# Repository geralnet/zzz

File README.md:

zZz
===

Geral.NET zZz Home Automation

PLEASE NOTE:
You are free to help us and we are glad you do;
however, you abdcate any intellectual property or ownership of
any material you submit to us. We will gladly take it as a without-strings attached donation.

*** This project is at version 0.0, so yeah, just started! ***

- HARDWARE
All schematics and DYO (easy to homebrew) board layouts are provided.
Not required, but suggested connection to an Arduino (ethernet model or with shield).

- FIRMWARE
Basic controller for Arduino with Ethernet provided with source code.
Your can adapt it further according to your needs.

- COMPUTER SOFTWARE
Java cross-platform control software.
The source code is provided and you are free to adapt to your needs.

- TABLET / SMARTPHONE APPS
The source code of all apps will be distributed.
Please note that our official app may not be free to download,
but you can compile and install it on your own (instructions provided).

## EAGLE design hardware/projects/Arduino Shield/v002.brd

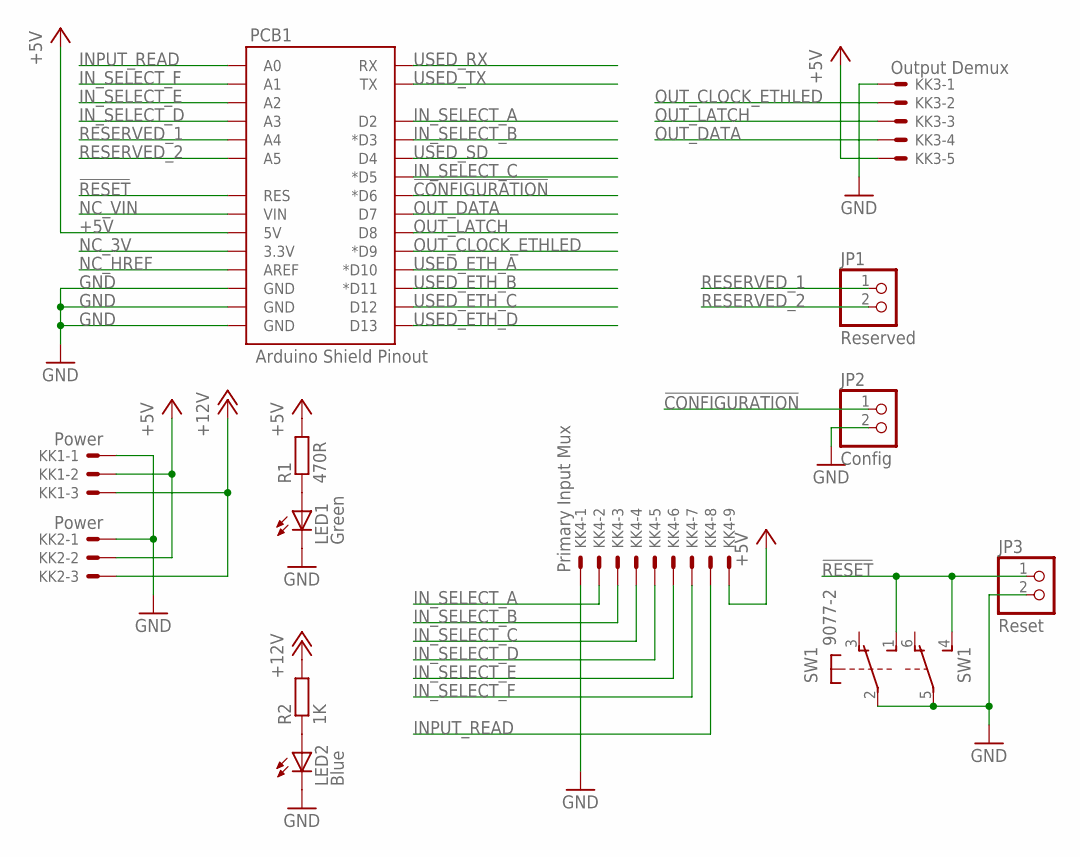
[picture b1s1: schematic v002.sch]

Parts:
JP1: Reserved; 1X02
JP2: Config; 1X02
JP3: Reset; 1X02
KK1, KK2: Power; 6410-03
KK3: Output Demux; 6410-05
KK4: Primary Input Mux; 6410-09
LED1: Green; LED3MM
LED2: Blue; LED3MM
PCB1: Arduino Shield Pinout; DUEMILANOVE_SHIELD_LONGPADS
R1: 470R; 0204/7
R2: 1K; 0204/7
SW1: 9077-2

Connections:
!CONFIGURATION: JP2.1, PCB1.D6 (*D6)
!RESET: JP3.1, PCB1.RES, SW1.1 (S), SW1.4 (S)
+5V: KK1.2, KK2.2, KK3.5, KK4.9, PCB1.5V, R1.2
+12V: KK1.3, KK2.3, R2.2
GND: JP2.2, JP3.2, KK1.1, KK2.1, KK3.1, KK4.1, LED1.K (C), LED2.K (C), PCB1.GND@0 (GND), PCB1.GND@1 (GND), PCB1.GND@2 (GND), SW1.2, SW1.5
INPUT_READ: KK4.8, PCB1.A0
IN_SELECT_A: KK4.2, PCB1.D2
IN_SELECT_B: KK4.3, PCB1.D3 (*D3)
IN_SELECT_C: KK4.4, PCB1.D5 (*D5)
IN_SELECT_D: KK4.5, PCB1.A3
IN_SELECT_E: KK4.6, PCB1.A2
IN_SELECT_F: KK4.7, PCB1.A1
N-L1: LED1.A, R1.1
N-L2: LED2.A, R2.1
NC_3V: PCB1.3.3V
NC_HREF: PCB1.AREF
NC_VIN: PCB1.VIN
OUT_CLOCK_ETHLED: KK3.2, PCB1.D9 (*D9)
OUT_DATA: KK3.4, PCB1.D7
OUT_LATCH: KK3.3, PCB1.D8
RESERVED_1: JP1.1, PCB1.A4
RESERVED_2: JP1.2, PCB1.A5
USED_ETH_A: PCB1.D10 (*D10)
USED_ETH_B: PCB1.D11 (*D11)
USED_ETH_C: PCB1.D12
USED_ETH_D: PCB1.D13
USED_RX: PCB1.RX
USED_SD: PCB1.D4
USED_TX: PCB1.TX

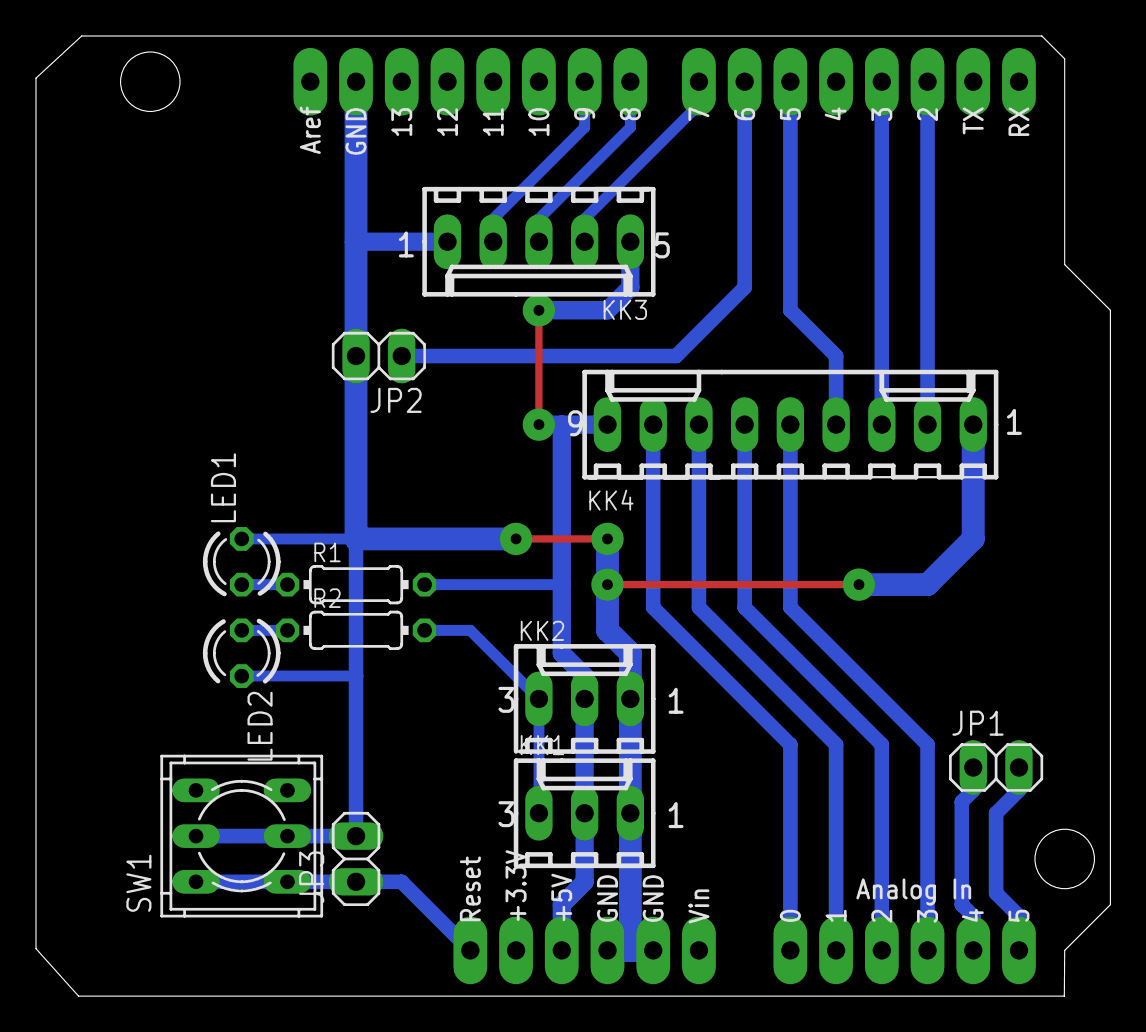
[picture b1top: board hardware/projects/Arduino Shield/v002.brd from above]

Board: 2 copper layers, 59.7 x 53.3 mm, 13 parts (0 on the bottom side), 19 nets.

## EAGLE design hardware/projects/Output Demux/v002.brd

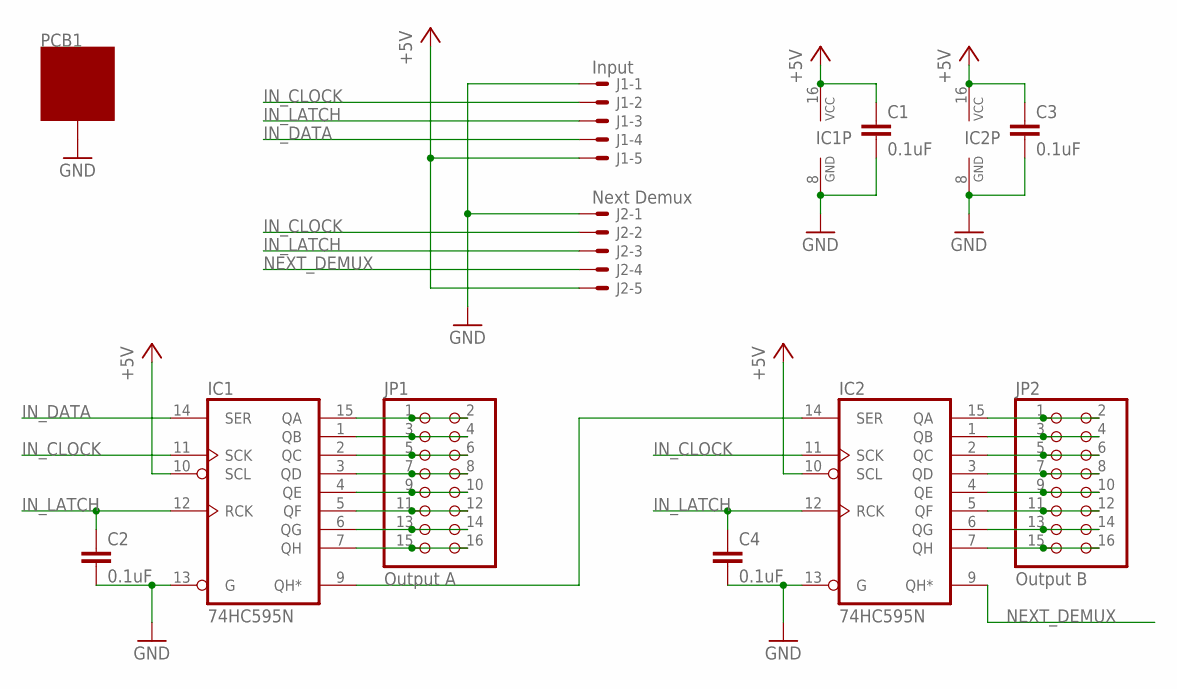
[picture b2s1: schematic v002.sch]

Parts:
C1, C2, C3, C4: 0.1uF; C050-024X044
IC1, IC2: 74HC595N; DIL16
J1: Input; 6410-05
J2: Next Demux; 6410-05
JP1: Output A; 2X08
JP2: Output B; 2X08
PCB1: ZZZ_MODULE05X05; ZZZ_MODULE_05X05

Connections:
+5V: C1.1, C3.1, IC1.10 (SCL), IC1.16 (VCC), IC2.10 (SCL), IC2.16 (VCC), J1.5, J2.5
GND: C1.2, C2.2, C3.2, C4.2, IC1.8 (GND), IC1.13 (G), IC2.8 (GND), IC2.13 (G), J1.1, J2.1, PCB1.GND@1, PCB1.GND@2, PCB1.GND@3, PCB1.GND@4, PCB1.GND@5, PCB1.GND@6, PCB1.GND@7, PCB1.GND@8
IN_CLOCK: IC1.11 (SCK), IC2.11 (SCK), J1.2, J2.2
IN_DATA: IC1.14 (SER), J1.4
IN_LATCH: C2.1, C4.1, IC1.12 (RCK), IC2.12 (RCK), J1.3, J2.3
unnamed: IC1.15 (QA), JP1.1, JP1.2
unnamed: IC1.1 (QB), JP1.3, JP1.4
unnamed: IC1.2 (QC), JP1.5, JP1.6
unnamed: IC1.3 (QD), JP1.7, JP1.8
unnamed: IC1.4 (QE), JP1.9, JP1.10
unnamed: IC1.5 (QF), JP1.11, JP1.12
unnamed: IC1.6 (QG), JP1.13, JP1.14
unnamed: IC1.7 (QH), JP1.15, JP1.16
unnamed: IC2.15 (QA), JP2.1, JP2.2
unnamed: IC2.1 (QB), JP2.3, JP2.4
unnamed: IC2.2 (QC), JP2.5, JP2.6
unnamed: IC2.3 (QD), JP2.7, JP2.8
unnamed: IC2.4 (QE), JP2.9, JP2.10
unnamed: IC2.5 (QF), JP2.11, JP2.12
unnamed: IC2.6 (QG), JP2.13, JP2.14
unnamed: IC2.7 (QH), JP2.15, JP2.16
unnamed: IC1.9 (QH*), IC2.14 (SER)
NEXT_DEMUX: IC2.9 (QH*), J2.4

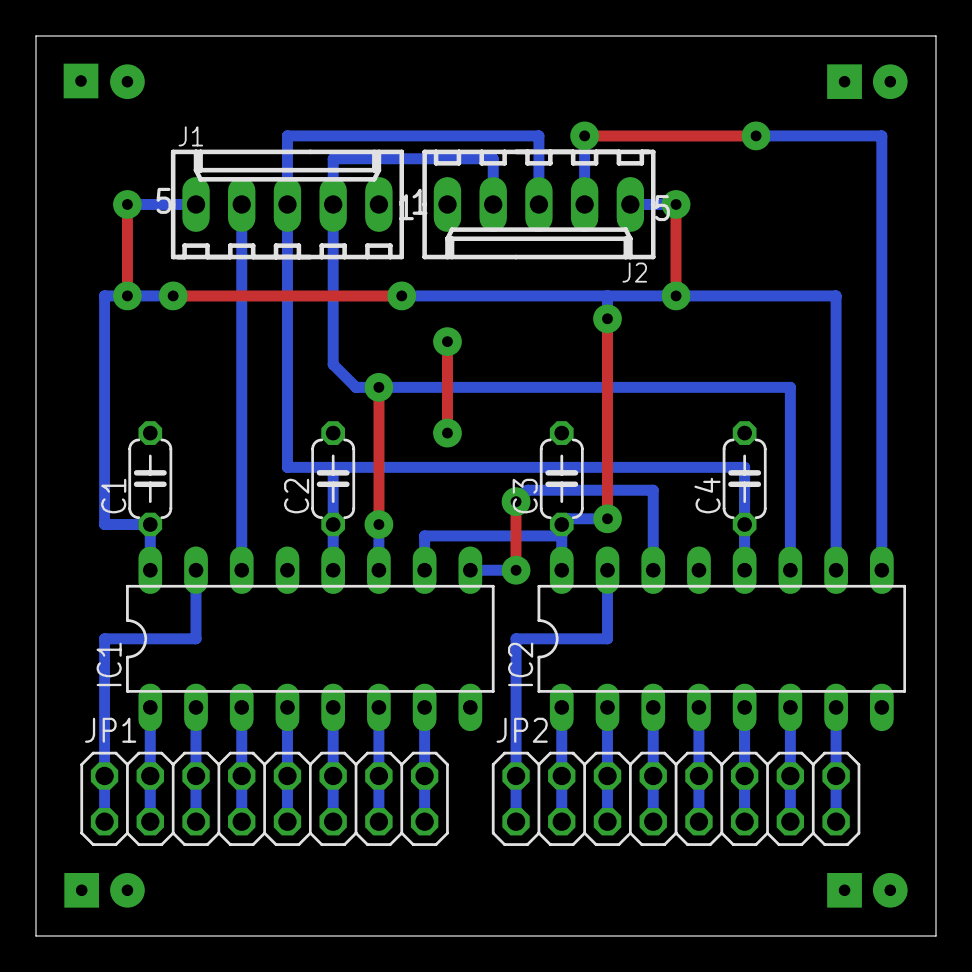
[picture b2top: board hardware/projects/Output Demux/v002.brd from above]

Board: 2 copper layers, 50.0 x 50.0 mm, 11 parts (0 on the bottom side), 23 nets.

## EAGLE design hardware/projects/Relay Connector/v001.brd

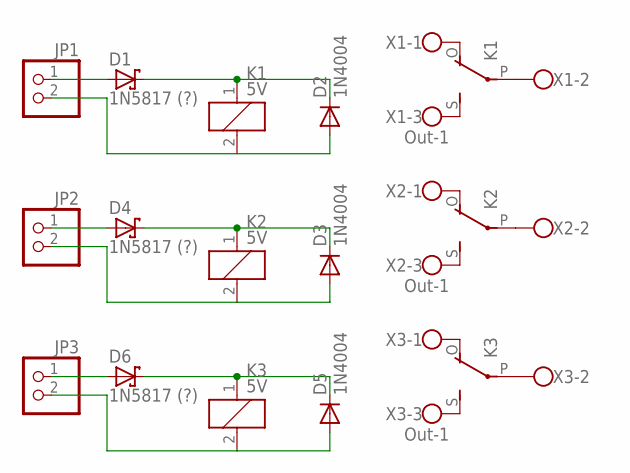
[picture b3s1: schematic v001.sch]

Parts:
D1, D4, D6: 1N5817 (?); DO41-7.6
D2, D3, D5: 1N4004; DO41-10
JP1, JP2, JP3: PINHD-1X2; 1X02
K1, K2, K3: 5V; G5LE
X1, X2, X3: Out-1; W237-103

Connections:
unnamed: K1.P, X1.2
unnamed: K1.O, X1.1
unnamed: K1.S, X1.3
unnamed: D1.A, JP1.1
unnamed: D2.A, JP1.2, K1.2
unnamed: D1.C, D2.C, K1.1
unnamed: K2.P, X2.2
unnamed: K2.O, X2.1
unnamed: K2.S, X2.3
unnamed: D4.A, JP2.1
unnamed: D3.A, JP2.2, K2.2
unnamed: D3.C, D4.C, K2.1
unnamed: K3.P, X3.2
unnamed: K3.O, X3.1
unnamed: K3.S, X3.3
unnamed: D6.A, JP3.1
unnamed: D5.A, JP3.2, K3.2
unnamed: D5.C, D6.C, K3.1

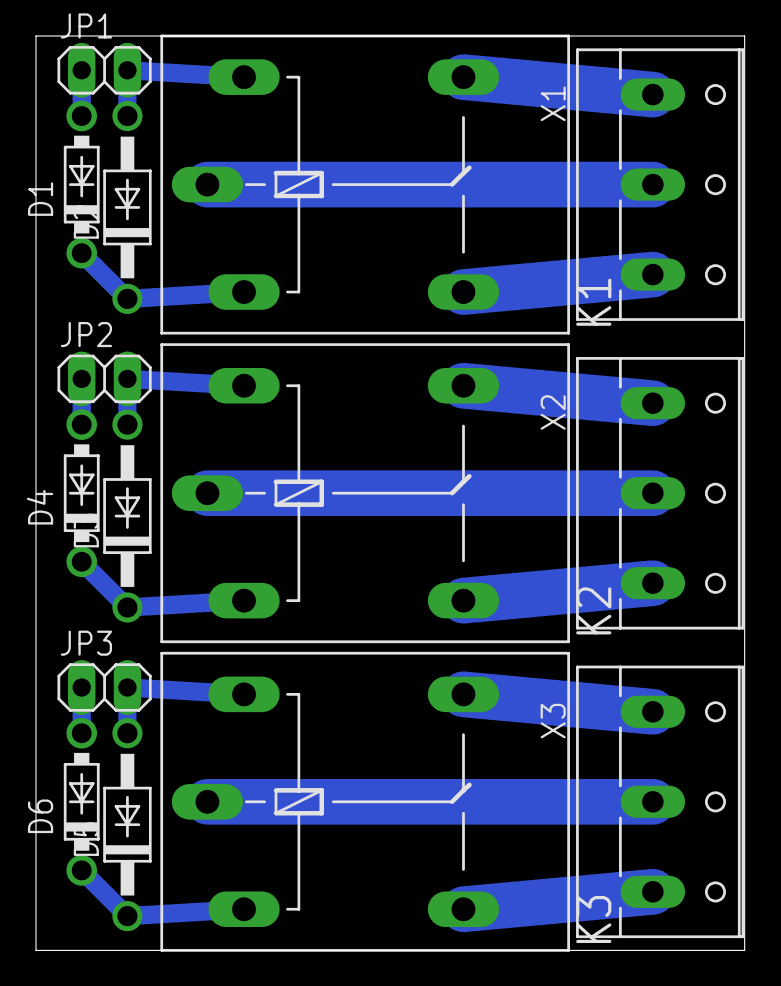
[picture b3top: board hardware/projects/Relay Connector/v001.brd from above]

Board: 2 copper layers, 39.4 x 50.8 mm, 15 parts (0 on the bottom side), 18 nets.

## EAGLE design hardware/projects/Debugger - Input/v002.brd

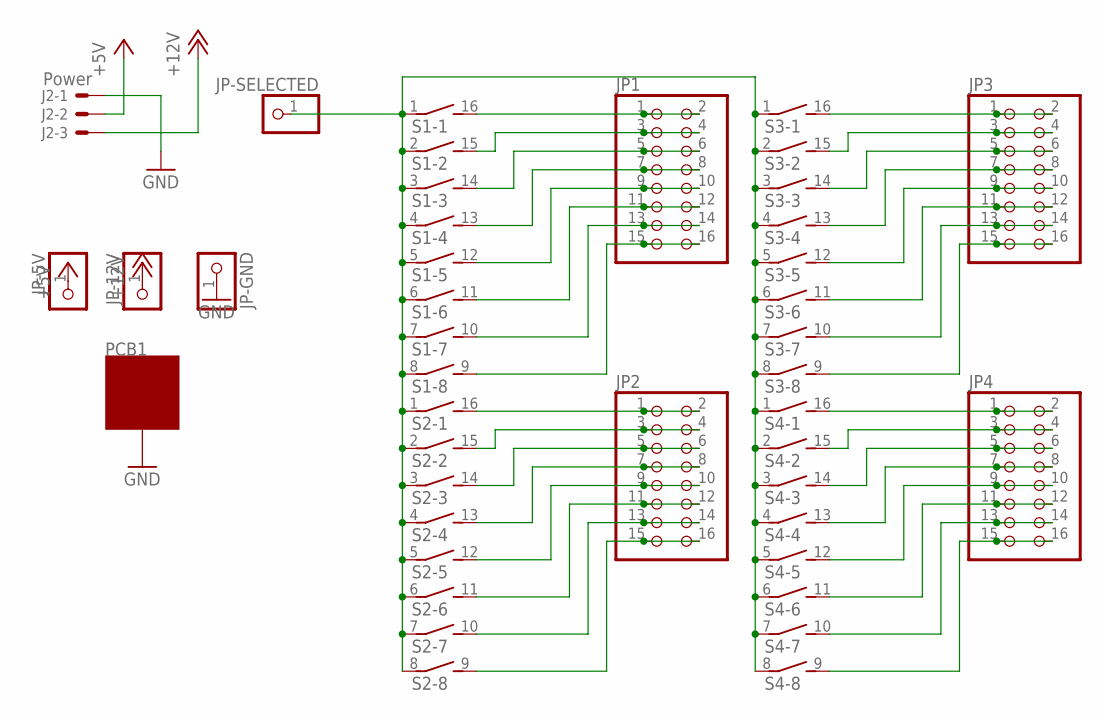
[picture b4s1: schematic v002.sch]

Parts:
J2: Power; 6410-03
JP1, JP2, JP3, JP4: PINHD-2X8; 2X08
JP-5V, JP-12V: PINHD-1X1; 1X01
JP-GND: PINHD-1X1; 1X01
JP-SELECTED: PINHD-1X1; 1X01
PCB1: ZZZ_MODULE05X05; ZZZ_MODULE_05X05
S1, S2, S3, S4: DIP08S

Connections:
+5V: J2.2, JP-5V.1
+12V: J2.3, JP-12V.1
GND: J2.1, JP-GND.1, PCB1.GND@1, PCB1.GND@2, PCB1.GND@3, PCB1.GND@4, PCB1.GND@5, PCB1.GND@6, PCB1.GND@7, PCB1.GND@8
unnamed: JP3.1, JP3.2, S3.16 (2)
unnamed: JP3.3, JP3.4, S3.15 (2)
unnamed: JP1.1, JP1.2, S1.16 (2)
unnamed: JP1.3, JP1.4, S1.15 (2)
unnamed: JP1.5, JP1.6, S1.14 (2)
unnamed: JP1.7, JP1.8, S1.13 (2)
unnamed: JP1.9, JP1.10, S1.12 (2)
unnamed: JP1.11, JP1.12, S1.11 (2)
unnamed: JP1.13, JP1.14, S1.10 (2)
unnamed: JP1.15, JP1.16, S1.9 (2)
unnamed: JP2.1, JP2.2, S2.16 (2)
unnamed: JP2.3, JP2.4, S2.15 (2)
unnamed: JP2.5, JP2.6, S2.14 (2)
unnamed: JP2.7, JP2.8, S2.13 (2)
unnamed: JP2.9, JP2.10, S2.12 (2)
unnamed: JP2.11, JP2.12, S2.11 (2)
unnamed: JP2.13, JP2.14, S2.10 (2)
unnamed: JP2.15, JP2.16, S2.9 (2)
unnamed: JP3.5, JP3.6, S3.14 (2)
unnamed: JP3.7, JP3.8, S3.13 (2)
unnamed: JP3.9, JP3.10, S3.12 (2)
unnamed: JP3.11, JP3.12, S3.11 (2)
unnamed: JP3.13, JP3.14, S3.10 (2)
unnamed: JP3.15, JP3.16, S3.9 (2)
unnamed: JP4.1, JP4.2, S4.16 (2)
unnamed: JP4.3, JP4.4, S4.15 (2)
unnamed: JP4.5, JP4.6, S4.14 (2)
unnamed: JP4.7, JP4.8, S4.13 (2)
unnamed: JP4.9, JP4.10, S4.12 (2)
unnamed: JP4.11, JP4.12, S4.11 (2)
unnamed: JP4.13, JP4.14, S4.10 (2)
unnamed: JP4.15, JP4.16, S4.9 (2)
unnamed: JP-SELECTED.1, S1.1, S1.2 (1), S1.3 (1), S1.4 (1), S1.5 (1), S1.6 (1), S1.7 (1), S1.8 (1), S2.1, S2.2 (1), S2.3 (1), S2.4 (1), S2.5 (1), S2.6 (1), S2.7 (1), S2.8 (1), S3.1, S3.2 (1), S3.3 (1), S3.4 (1), S3.5 (1), S3.6 (1), S3.7 (1), S3.8 (1), S4.1, S4.2 (1), S4.3 (1), S4.4 (1), S4.5 (1), S4.6 (1), S4.7 (1), S4.8 (1)

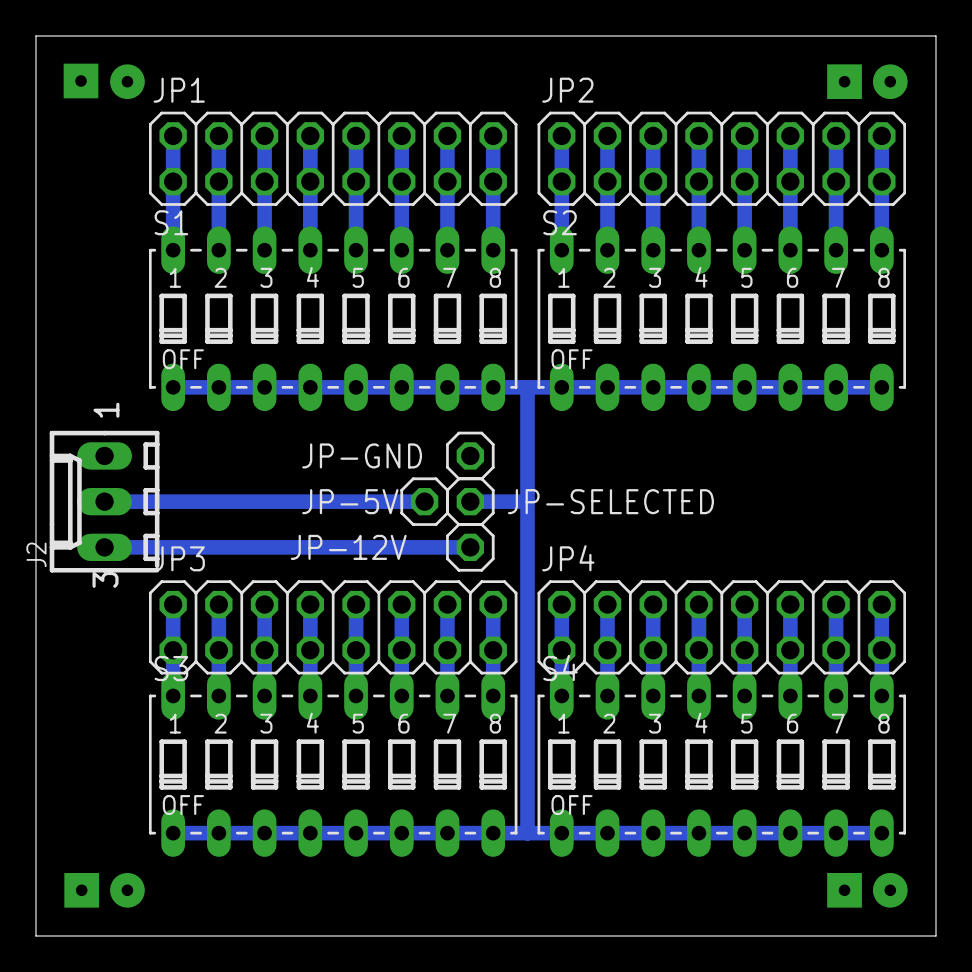
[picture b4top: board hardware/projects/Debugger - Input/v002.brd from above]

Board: 2 copper layers, 50.0 x 50.0 mm, 14 parts (0 on the bottom side), 36 nets.

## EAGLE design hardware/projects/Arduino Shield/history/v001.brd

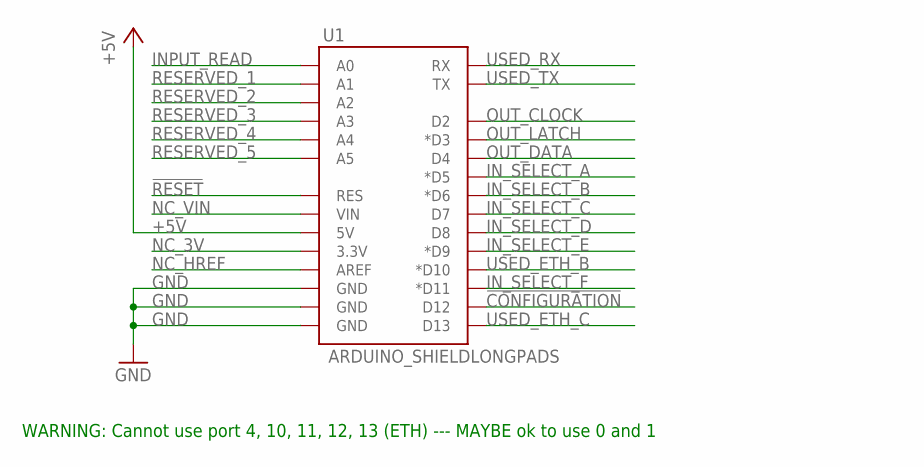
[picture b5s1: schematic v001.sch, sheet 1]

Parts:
U1: ARDUINO_SHIELDLONGPADS; DUEMILANOVE_SHIELD_LONGPADS

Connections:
!CONFIGURATION: U1.D12; also elsewhere on the board
!RESET: U1.RES; also elsewhere on the board
+5V: U1.5V; also elsewhere on the board
GND: U1.GND@0 (GND), U1.GND@1 (GND), U1.GND@2 (GND); also elsewhere on the board
INPUT_READ: U1.A0; also elsewhere on the board
IN_SELECT_A: U1.D5 (*D5); also elsewhere on the board
IN_SELECT_B: U1.D6 (*D6); also elsewhere on the board
IN_SELECT_C: U1.D7; also elsewhere on the board
IN_SELECT_D: U1.D8; also elsewhere on the board
IN_SELECT_E: U1.D9 (*D9); also elsewhere on the board
IN_SELECT_F: U1.D11 (*D11); also elsewhere on the board
NC_3V: U1.3.3V
NC_HREF: U1.AREF
NC_VIN: U1.VIN
OUT_CLOCK: U1.D2; also elsewhere on the board
OUT_DATA: U1.D4; also elsewhere on the board
OUT_LATCH: U1.D3 (*D3); also elsewhere on the board
RESERVED_1: U1.A1; also elsewhere on the board
RESERVED_2: U1.A2; also elsewhere on the board
RESERVED_3: U1.A3; also elsewhere on the board
RESERVED_4: U1.A4; also elsewhere on the board
RESERVED_5: U1.A5; also elsewhere on the board
USED_ETH_B: U1.D10 (*D10)
USED_ETH_C: U1.D13
USED_RX: U1.RX
USED_TX: U1.TX

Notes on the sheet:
WARNING: Cannot use port 4, 10, 11, 12, 13 (ETH) --- MAYBE ok to use 0 and 1

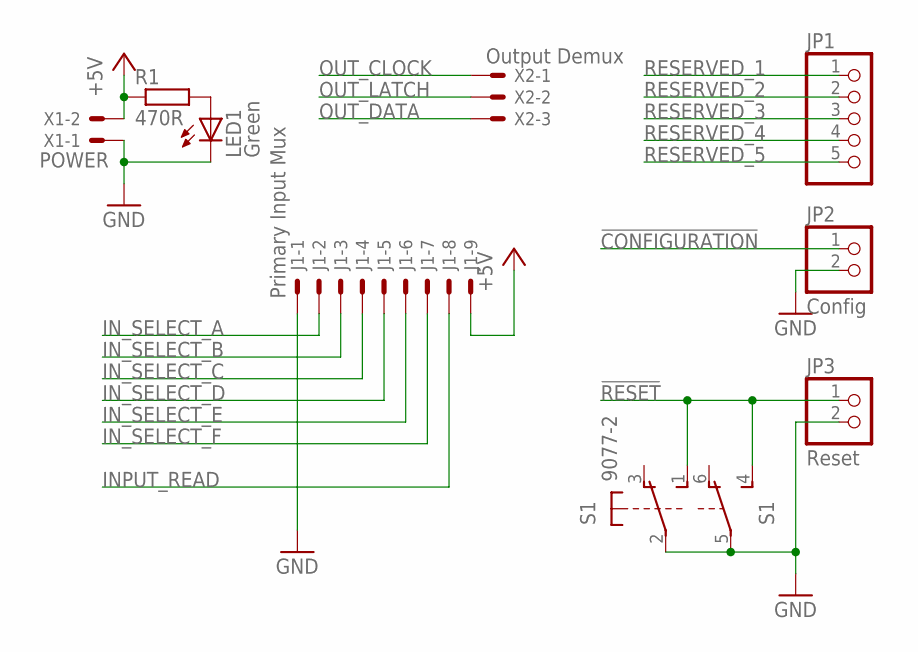
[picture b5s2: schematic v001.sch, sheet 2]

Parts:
J1: Primary Input Mux; 6410-09
JP1: PINHD-1X5; 1X05
JP2: Config; 1X02
JP3: Reset; 1X02
LED1: Green; LED3MM
R1: 470R; 0204/7
S1: 9077-2
X1: POWER; 22-23-2021
X2: Output Demux; 22-23-2031

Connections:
!CONFIGURATION: JP2.1; also elsewhere on the board
!RESET: JP3.1, S1.1 (S), S1.4 (S); also elsewhere on the board
+5V: J1.9, R1.1, X1.2; also elsewhere on the board
GND: J1.1, JP2.2, JP3.2, LED1.K (C), S1.2, S1.5, X1.1; also elsewhere on the board
INPUT_READ: J1.8; also elsewhere on the board
IN_SELECT_A: J1.2; also elsewhere on the board
IN_SELECT_B: J1.3; also elsewhere on the board
IN_SELECT_C: J1.4; also elsewhere on the board
IN_SELECT_D: J1.5; also elsewhere on the board
IN_SELECT_E: J1.6; also elsewhere on the board
IN_SELECT_F: J1.7; also elsewhere on the board
unnamed: LED1.A, R1.2
OUT_CLOCK: X2.1; also elsewhere on the board
OUT_DATA: X2.3; also elsewhere on the board
OUT_LATCH: X2.2; also elsewhere on the board
RESERVED_1: JP1.1; also elsewhere on the board
RESERVED_2: JP1.2; also elsewhere on the board
RESERVED_3: JP1.3; also elsewhere on the board
RESERVED_4: JP1.4; also elsewhere on the board
RESERVED_5: JP1.5; also elsewhere on the board

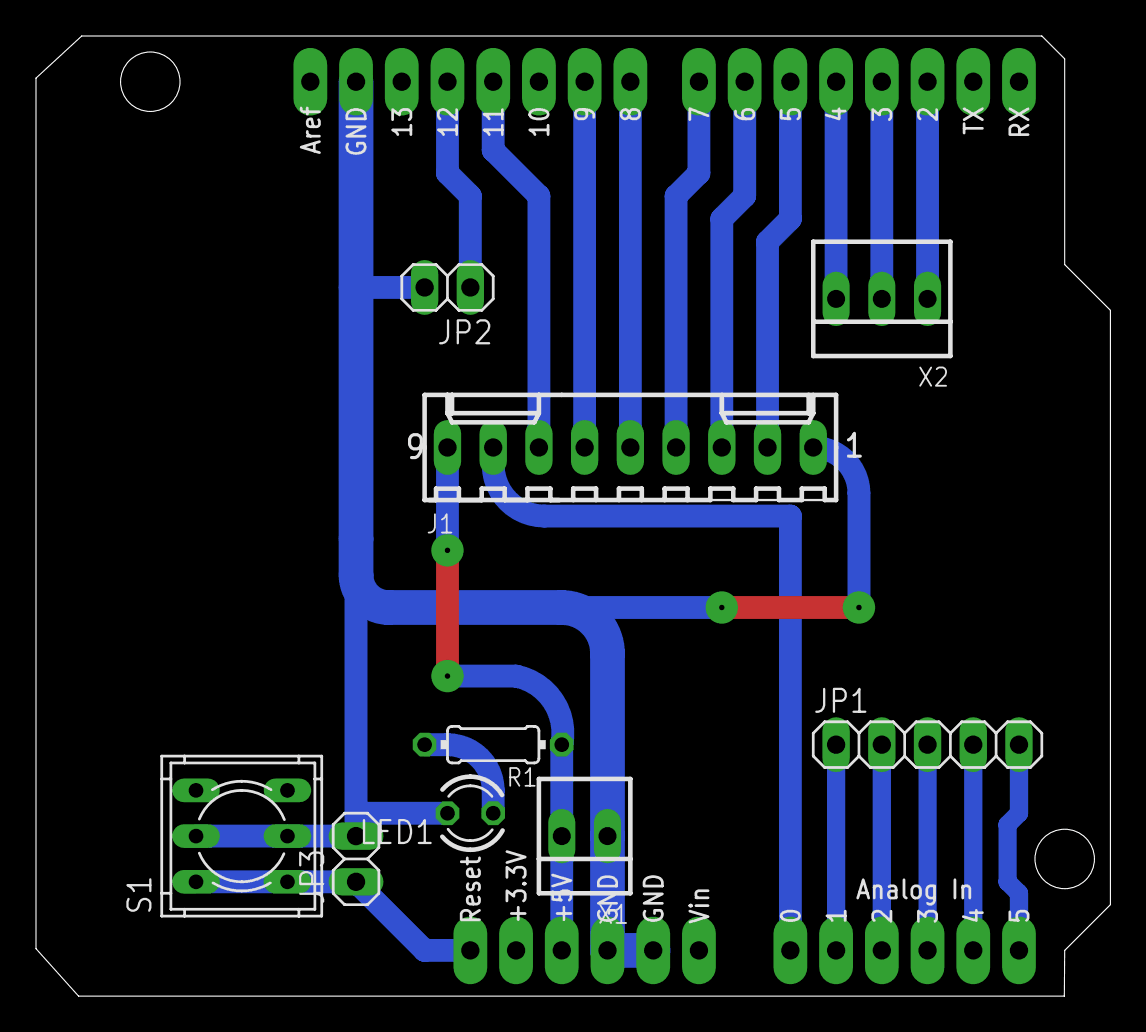
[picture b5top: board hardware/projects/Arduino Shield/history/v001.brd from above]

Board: 2 copper layers, 59.7 x 53.3 mm, 10 parts (0 on the bottom side), 20 nets.

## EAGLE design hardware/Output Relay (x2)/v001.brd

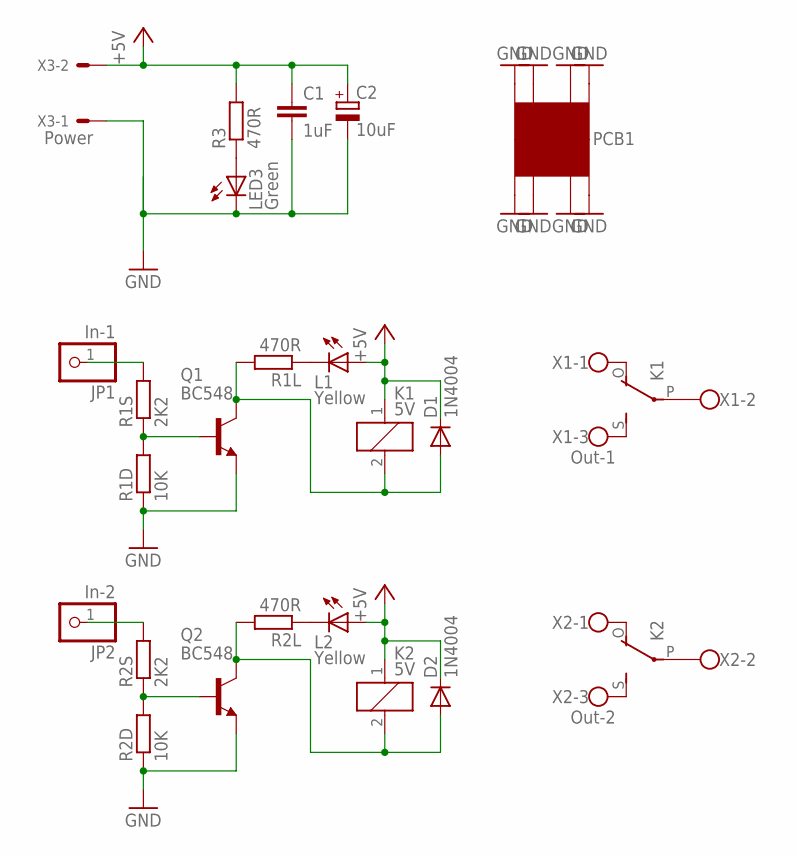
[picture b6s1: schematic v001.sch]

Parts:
C1: 1uF; C050-035X075
C2: 10uF; E2,5-5
D1, D2: 1N4004; DO41-10
JP1: In-1; 1X01
JP2: In-2; 1X01
K1, K2: 5V; G5LE
L1, L2: Yellow; LED3MM
LED3: Green; LED3MM
PCB1: PCB05X05; PCB_05X05
Q1, Q2: BC548; TO92-EBC
R1D, R2D: 10K; 0204/7
R1L, R2L: 470R; 0204/7
R1S, R2S: 2K2; 0204/7
R3: 470R; 0207/2V
X1: Out-1; W237-103
X2: Out-2; W237-103
X3: Power; 6410-02

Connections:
+5V: C1.1, C2.+, D1.C, D2.C, K1.1, K2.1, L1.A, L2.A, R3.2, X3.2
GND: C1.2, C2.-, LED3.K (C), PCB1.GND@1, PCB1.GND@2, PCB1.GND@3, PCB1.GND@4, PCB1.GND@5, PCB1.GND@6, PCB1.GND@7, PCB1.GND@8, Q1.E, Q2.E, R1D.1, R2D.1, X3.1
unnamed: K1.P, X1.2
unnamed: K1.O, X1.1
unnamed: K1.S, X1.3
unnamed: Q2.B, R2D.2, R2S.1
unnamed: JP2.1, R2S.2
unnamed: D2.A, K2.2, Q2.C, R2L.2
unnamed: L2.K (C), R2L.1
unnamed: K2.P, X2.2
unnamed: K2.S, X2.3
unnamed: K2.O, X2.1
unnamed: D1.A, K1.2, Q1.C, R1L.2
unnamed: Q1.B, R1D.2, R1S.1
unnamed: JP1.1, R1S.2
unnamed: L1.K (C), R1L.1
unnamed: LED3.A, R3.1

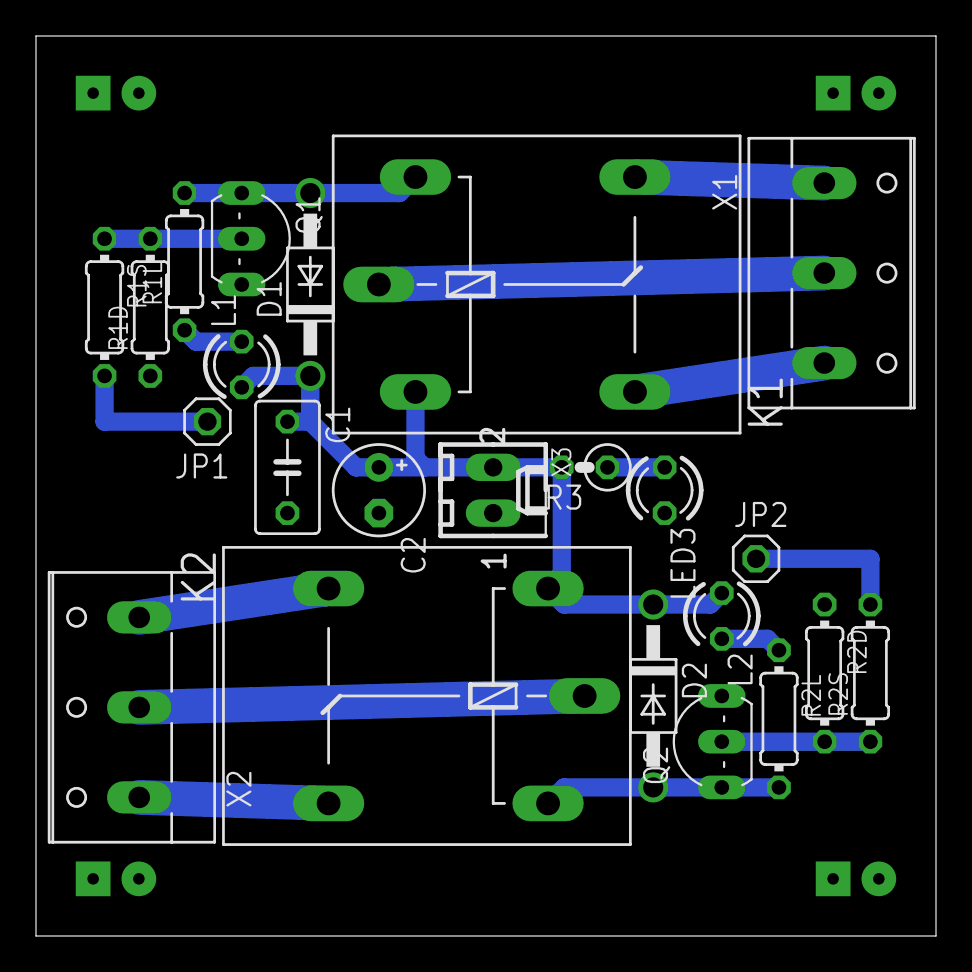
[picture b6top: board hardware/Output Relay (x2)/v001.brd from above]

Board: 2 copper layers, 50.0 x 50.0 mm, 24 parts (0 on the bottom side), 17 nets.

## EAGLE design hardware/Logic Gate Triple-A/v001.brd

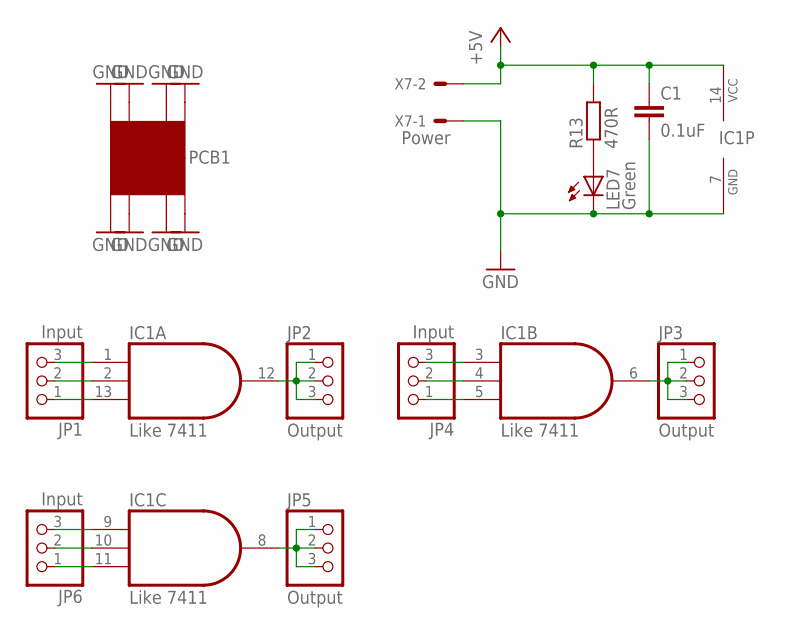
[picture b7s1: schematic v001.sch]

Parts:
C1: 0.1uF; C050-024X044
IC1: Like 7411; DIL14
JP1, JP4, JP6: Input; 1X03
JP2, JP3, JP5: Output; 1X03
LED7: Green; LED3MM
PCB1: PCB05X05; PCB_05X05
R13: 470R; 0204/7
X7: Power; 6410-02

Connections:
+5V: C1.1, IC1.14 (VCC), R13.2, X7.2
GND: C1.2, IC1.7 (GND), LED7.K (C), PCB1.GND@1, PCB1.GND@2, PCB1.GND@3, PCB1.GND@4, PCB1.GND@5, PCB1.GND@6, PCB1.GND@7, PCB1.GND@8, X7.1
unnamed: IC1.13 (I2), JP1.1
unnamed: IC1.2 (I1), JP1.2
unnamed: IC1.12 (O), JP2.1, JP2.2, JP2.3
unnamed: IC1.1 (I0), JP1.3
unnamed: LED7.A, R13.1
unnamed: IC1.5 (I2), JP4.1
unnamed: IC1.6 (O), JP3.1, JP3.2, JP3.3
unnamed: IC1.4 (I1), JP4.2
unnamed: IC1.3 (I0), JP4.3
unnamed: IC1.8 (O), JP5.1, JP5.2, JP5.3
unnamed: IC1.11 (I2), JP6.1
unnamed: IC1.10 (I1), JP6.2
unnamed: IC1.9 (I0), JP6.3

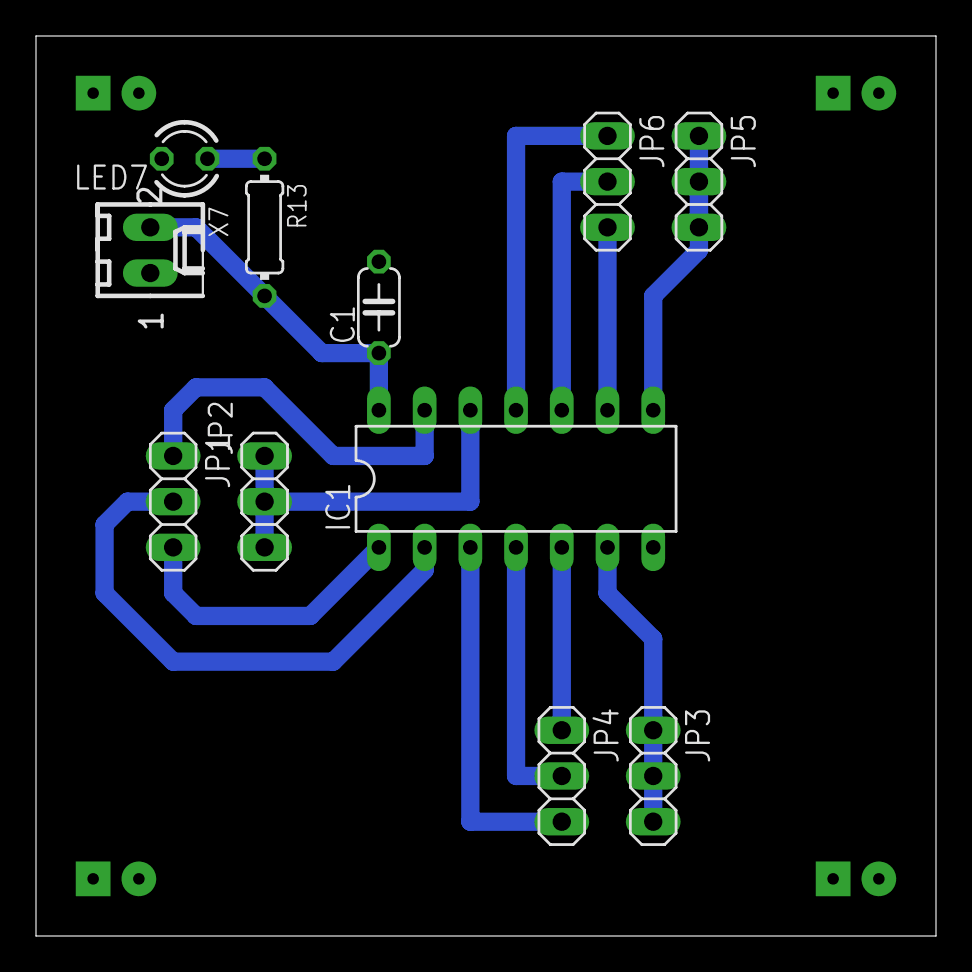
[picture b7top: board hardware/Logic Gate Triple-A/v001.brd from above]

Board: 2 copper layers, 50.0 x 50.0 mm, 12 parts (0 on the bottom side), 15 nets.

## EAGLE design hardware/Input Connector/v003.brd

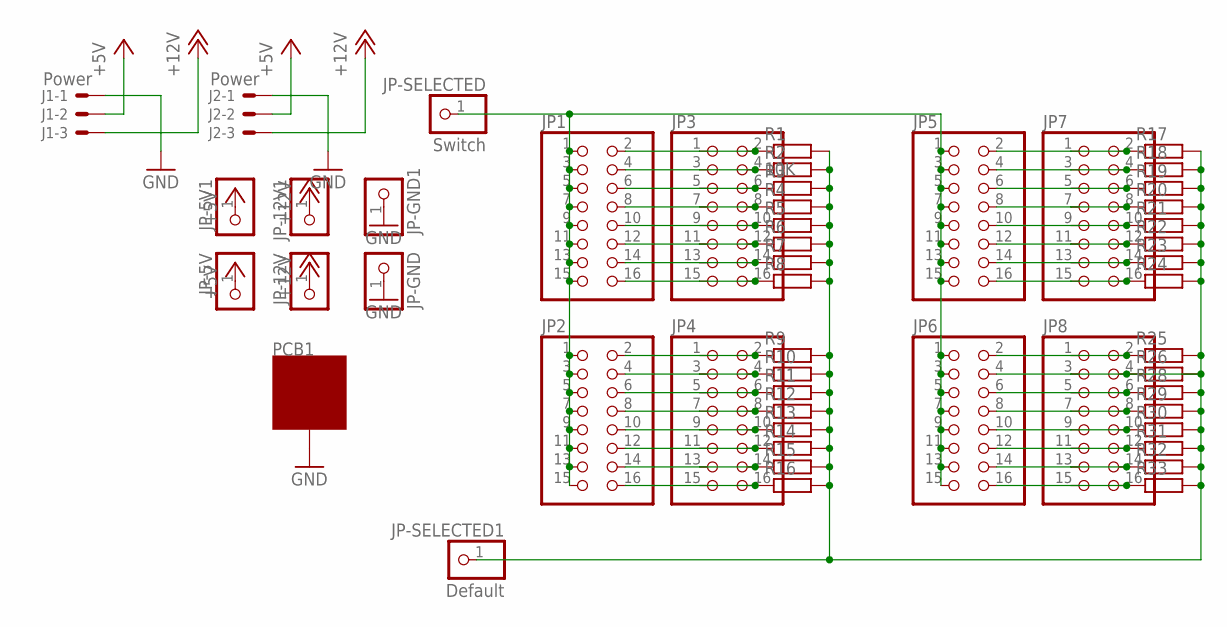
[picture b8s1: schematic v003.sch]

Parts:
J1, J2: Power; 6410-03
JP1, JP2, JP3, JP4, JP5, JP6, JP7, JP8: PINHD-2X8; 2X08
JP-5V, JP-5V1, JP-12V, JP-12V1: PINHD-1X1; 1X01
JP-GND, JP-GND1: PINHD-1X1; 1X01
JP-SELECTED: Switch; 1X01
JP-SELECTED1: Default; 1X01
PCB1: ZZZ_MODULE05X05; ZZZ_MODULE_05X05
R1: 10K; 0207/2V
R2, R3, R4, R5, R6, R7, R8, R9, R10, R11, R12, R13, R14, R15, R16, R17, R18, R19, R20, R21, R22, R23, R24, R25, R26, R28, R29, R30, R31, R32, R33: R-EU_0207/2V; 0207/2V

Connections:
+5V: J1.2, J2.2, JP-5V.1, JP-5V1.1
+12V: J1.3, J2.3, JP-12V.1, JP-12V1.1
GND: J1.1, J2.1, JP-GND.1, JP-GND1.1, PCB1.GND@1, PCB1.GND@2, PCB1.GND@3, PCB1.GND@4, PCB1.GND@5, PCB1.GND@6, PCB1.GND@7, PCB1.GND@8
unnamed: JP1.2, JP3.1, JP3.2, R1.1
unnamed: JP1.4, JP3.3, JP3.4, R2.1
unnamed: JP1.6, JP3.5, JP3.6, R3.1
unnamed: JP1.8, JP3.7, JP3.8, R4.1
unnamed: JP1.10, JP3.9, JP3.10, R5.1
unnamed: JP1.12, JP3.11, JP3.12, R6.1
unnamed: JP1.14, JP3.13, JP3.14, R7.1
unnamed: JP1.16, JP3.15, JP3.16, R8.1
unnamed: JP2.2, JP4.1, JP4.2, R9.1
unnamed: JP2.4, JP4.3, JP4.4, R10.1
unnamed: JP2.6, JP4.5, JP4.6, R11.1
unnamed: JP2.8, JP4.7, JP4.8, R12.1
unnamed: JP2.10, JP4.9, JP4.10, R13.1
unnamed: JP2.12, JP4.11, JP4.12, R14.1
unnamed: JP2.14, JP4.13, JP4.14, R15.1
unnamed: JP2.16, JP4.15, JP4.16, R16.1
unnamed: JP5.2, JP7.1, JP7.2, R17.1
unnamed: JP5.4, JP7.3, JP7.4, R18.1
unnamed: JP5.6, JP7.5, JP7.6, R19.1
unnamed: JP5.8, JP7.7, JP7.8, R20.1
unnamed: JP5.10, JP7.9, JP7.10, R21.1
unnamed: JP5.12, JP7.11, JP7.12, R22.1
unnamed: JP5.14, JP7.13, JP7.14, R23.1
unnamed: JP5.16, JP7.15, JP7.16, R24.1
unnamed: JP6.2, JP8.1, JP8.2, R25.1
unnamed: JP6.4, JP8.3, JP8.4, R26.1
unnamed: JP6.6, JP8.5, JP8.6, R28.1
unnamed: JP6.8, JP8.7, JP8.8, R29.1
unnamed: JP6.10, JP8.9, JP8.10, R30.1
unnamed: JP6.12, JP8.11, JP8.12, R31.1
unnamed: JP6.14, JP8.13, JP8.14, R32.1
unnamed: JP6.16, JP8.15, JP8.16, R33.1
unnamed: JP1.1, JP1.3, JP1.5, JP1.7, JP1.9, JP1.11, JP1.13, JP1.15, JP2.1, JP2.3, JP2.5, JP2.7, JP2.9, JP2.11, JP2.13, JP2.15, JP5.1, JP5.3, JP5.5, JP5.7, JP5.9, JP5.11, JP5.13, JP5.15, JP6.1, JP6.3, JP6.5, JP6.7, JP6.9, JP6.11, JP6.13, JP6.15, JP-SELECTED.1
unnamed: JP-SELECTED1.1, R1.2, R2.2, R3.2, R4.2, R5.2, R6.2, R7.2, R8.2, R9.2, R10.2, R11.2, R12.2, R13.2, R14.2, R15.2, R16.2, R17.2, R18.2, R19.2, R20.2, R21.2, R22.2, R23.2, R24.2, R25.2, R26.2, R28.2, R29.2, R30.2, R31.2, R32.2, R33.2

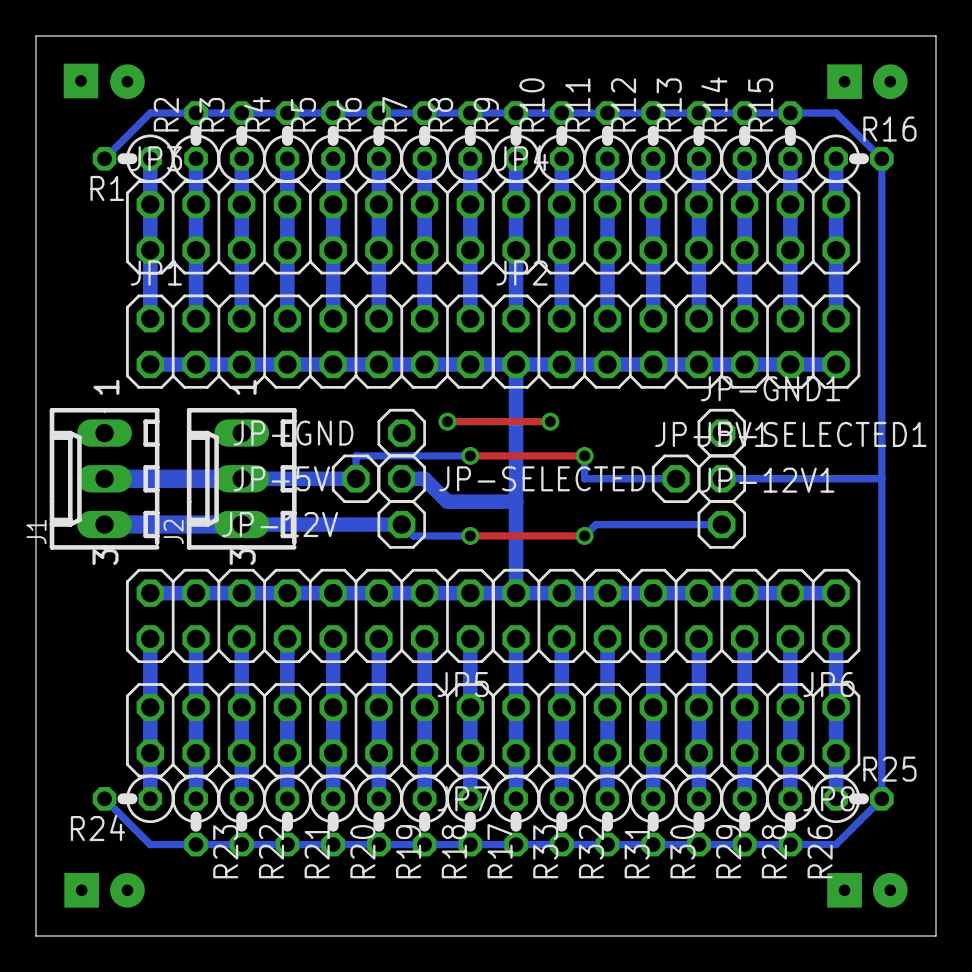
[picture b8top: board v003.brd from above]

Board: 2 copper layers, 50.0 x 50.0 mm, 51 parts (0 on the bottom side), 37 nets.

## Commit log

2013-07-30 initial tests
2013-07-31 Implemented some debugging arduino firmware. Started main arduino firmware, already responding some UDP messages. + A simple java UDP sender (hardcoded) for testing purposes.
2013-08-01 General Implementations
2013-08-07 Initial Programming...
2013-08-08 New implementation of android test application
2013-08-09 Separate hardware and software files
    Created two folders, software and hardware, to put PCB schematics and layout into hardware folder.
2013-08-09 Default configuration changed.
2013-08-09 Added .cfg to gitignore
2013-08-09 Added hardware files.
2013-08-11 Synchronize

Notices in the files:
parts and their libraries:
SparkFun-Boards: Licensing: CC v3.0 Share-Alike You are welcome to use this library for commercial purposes.
